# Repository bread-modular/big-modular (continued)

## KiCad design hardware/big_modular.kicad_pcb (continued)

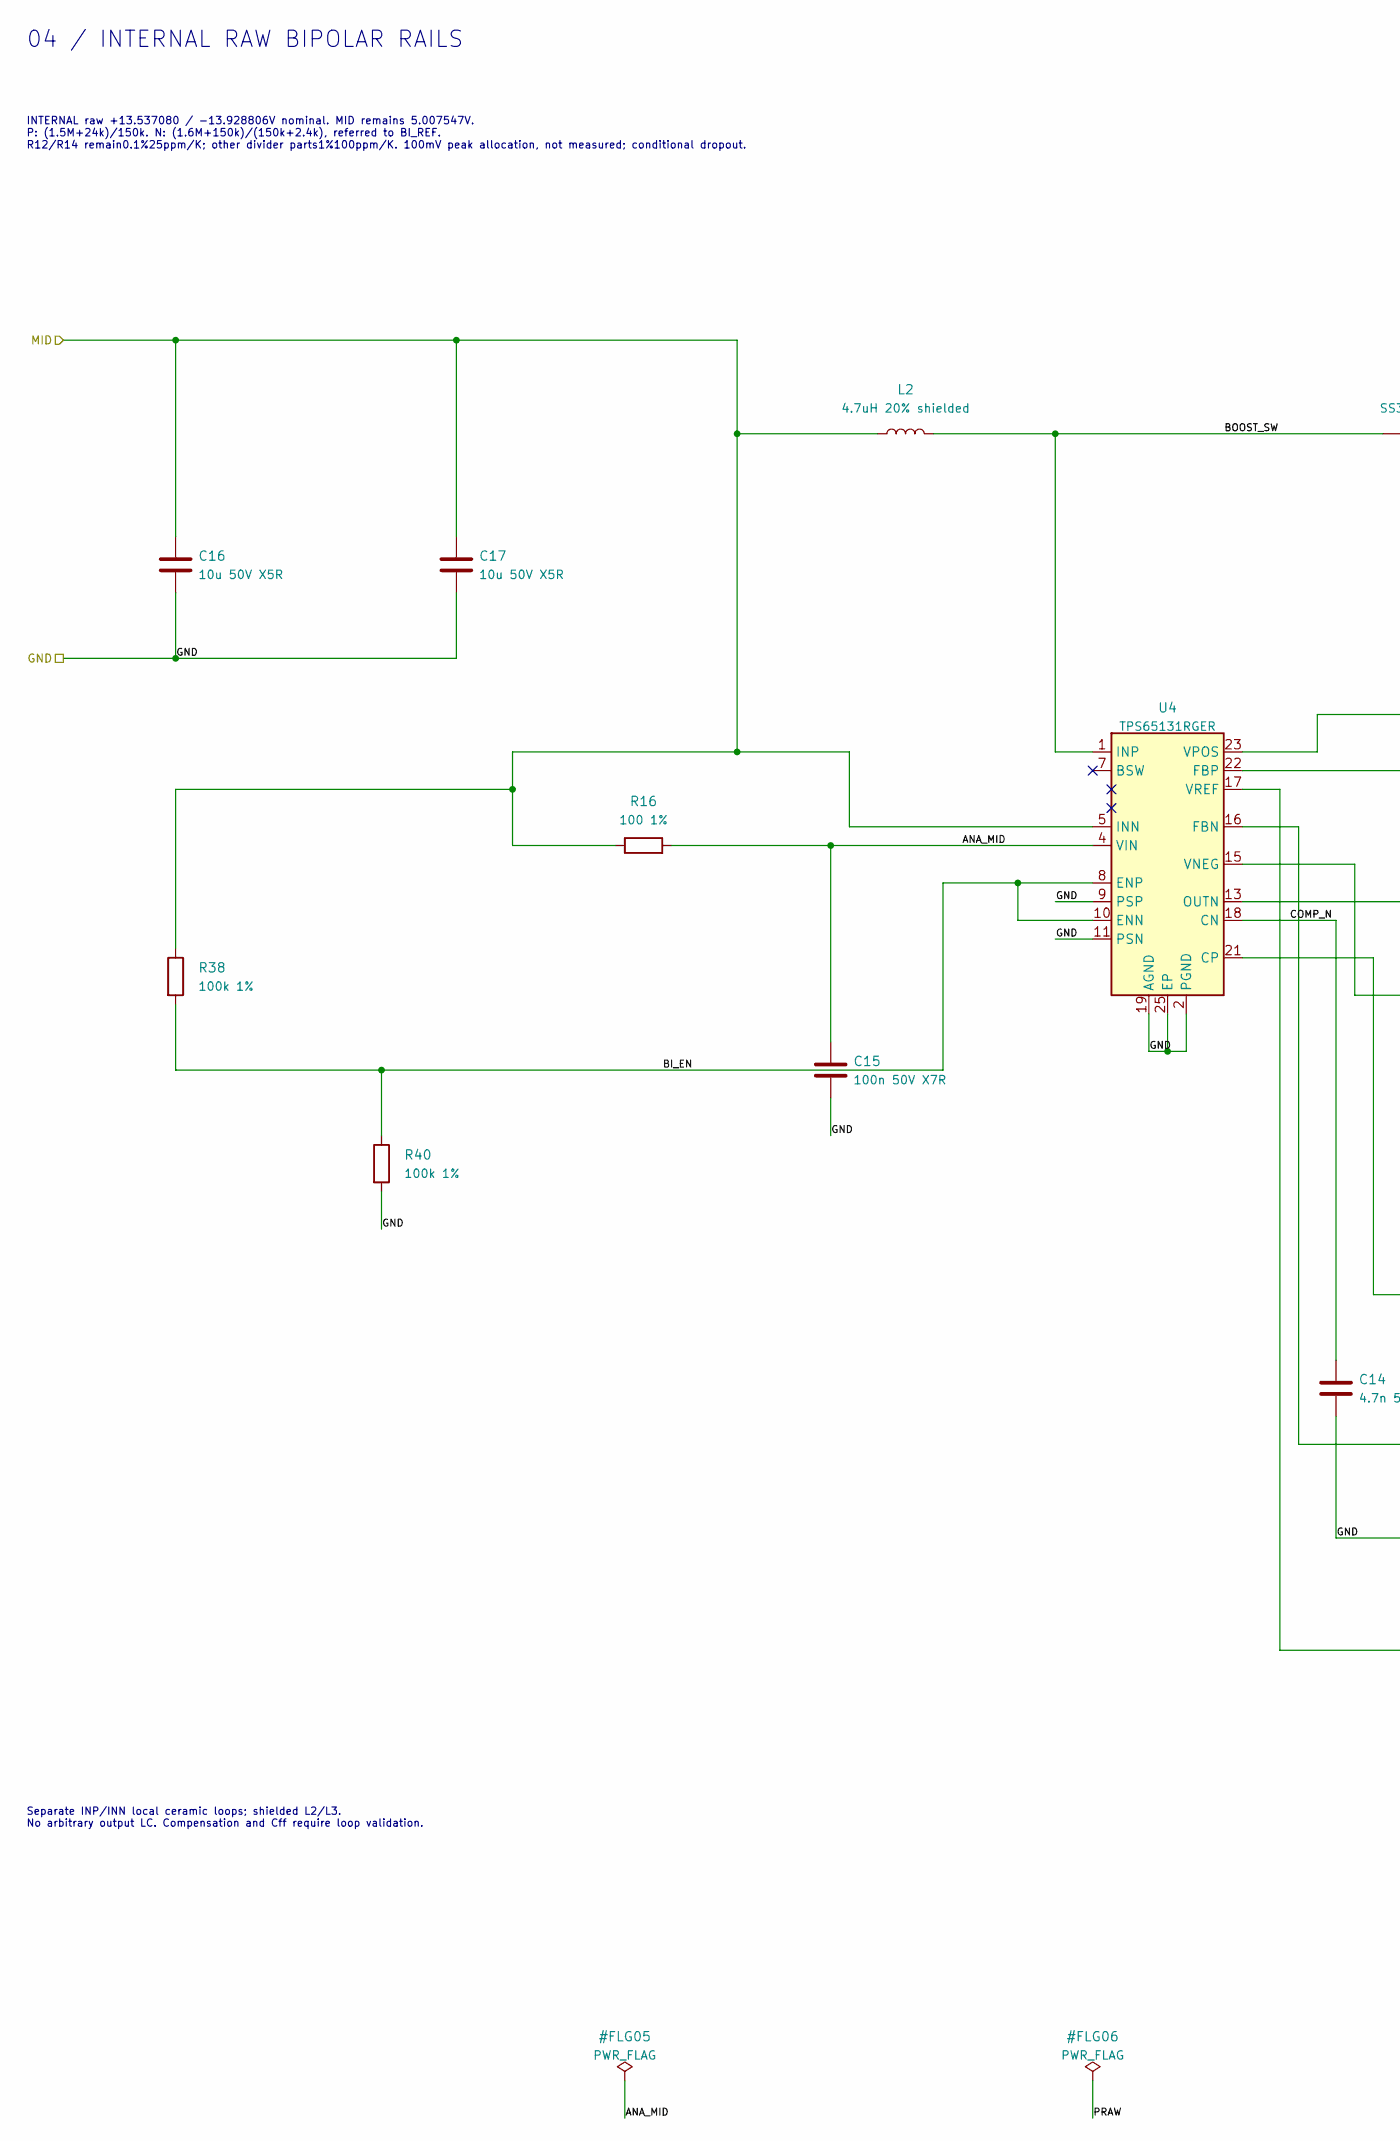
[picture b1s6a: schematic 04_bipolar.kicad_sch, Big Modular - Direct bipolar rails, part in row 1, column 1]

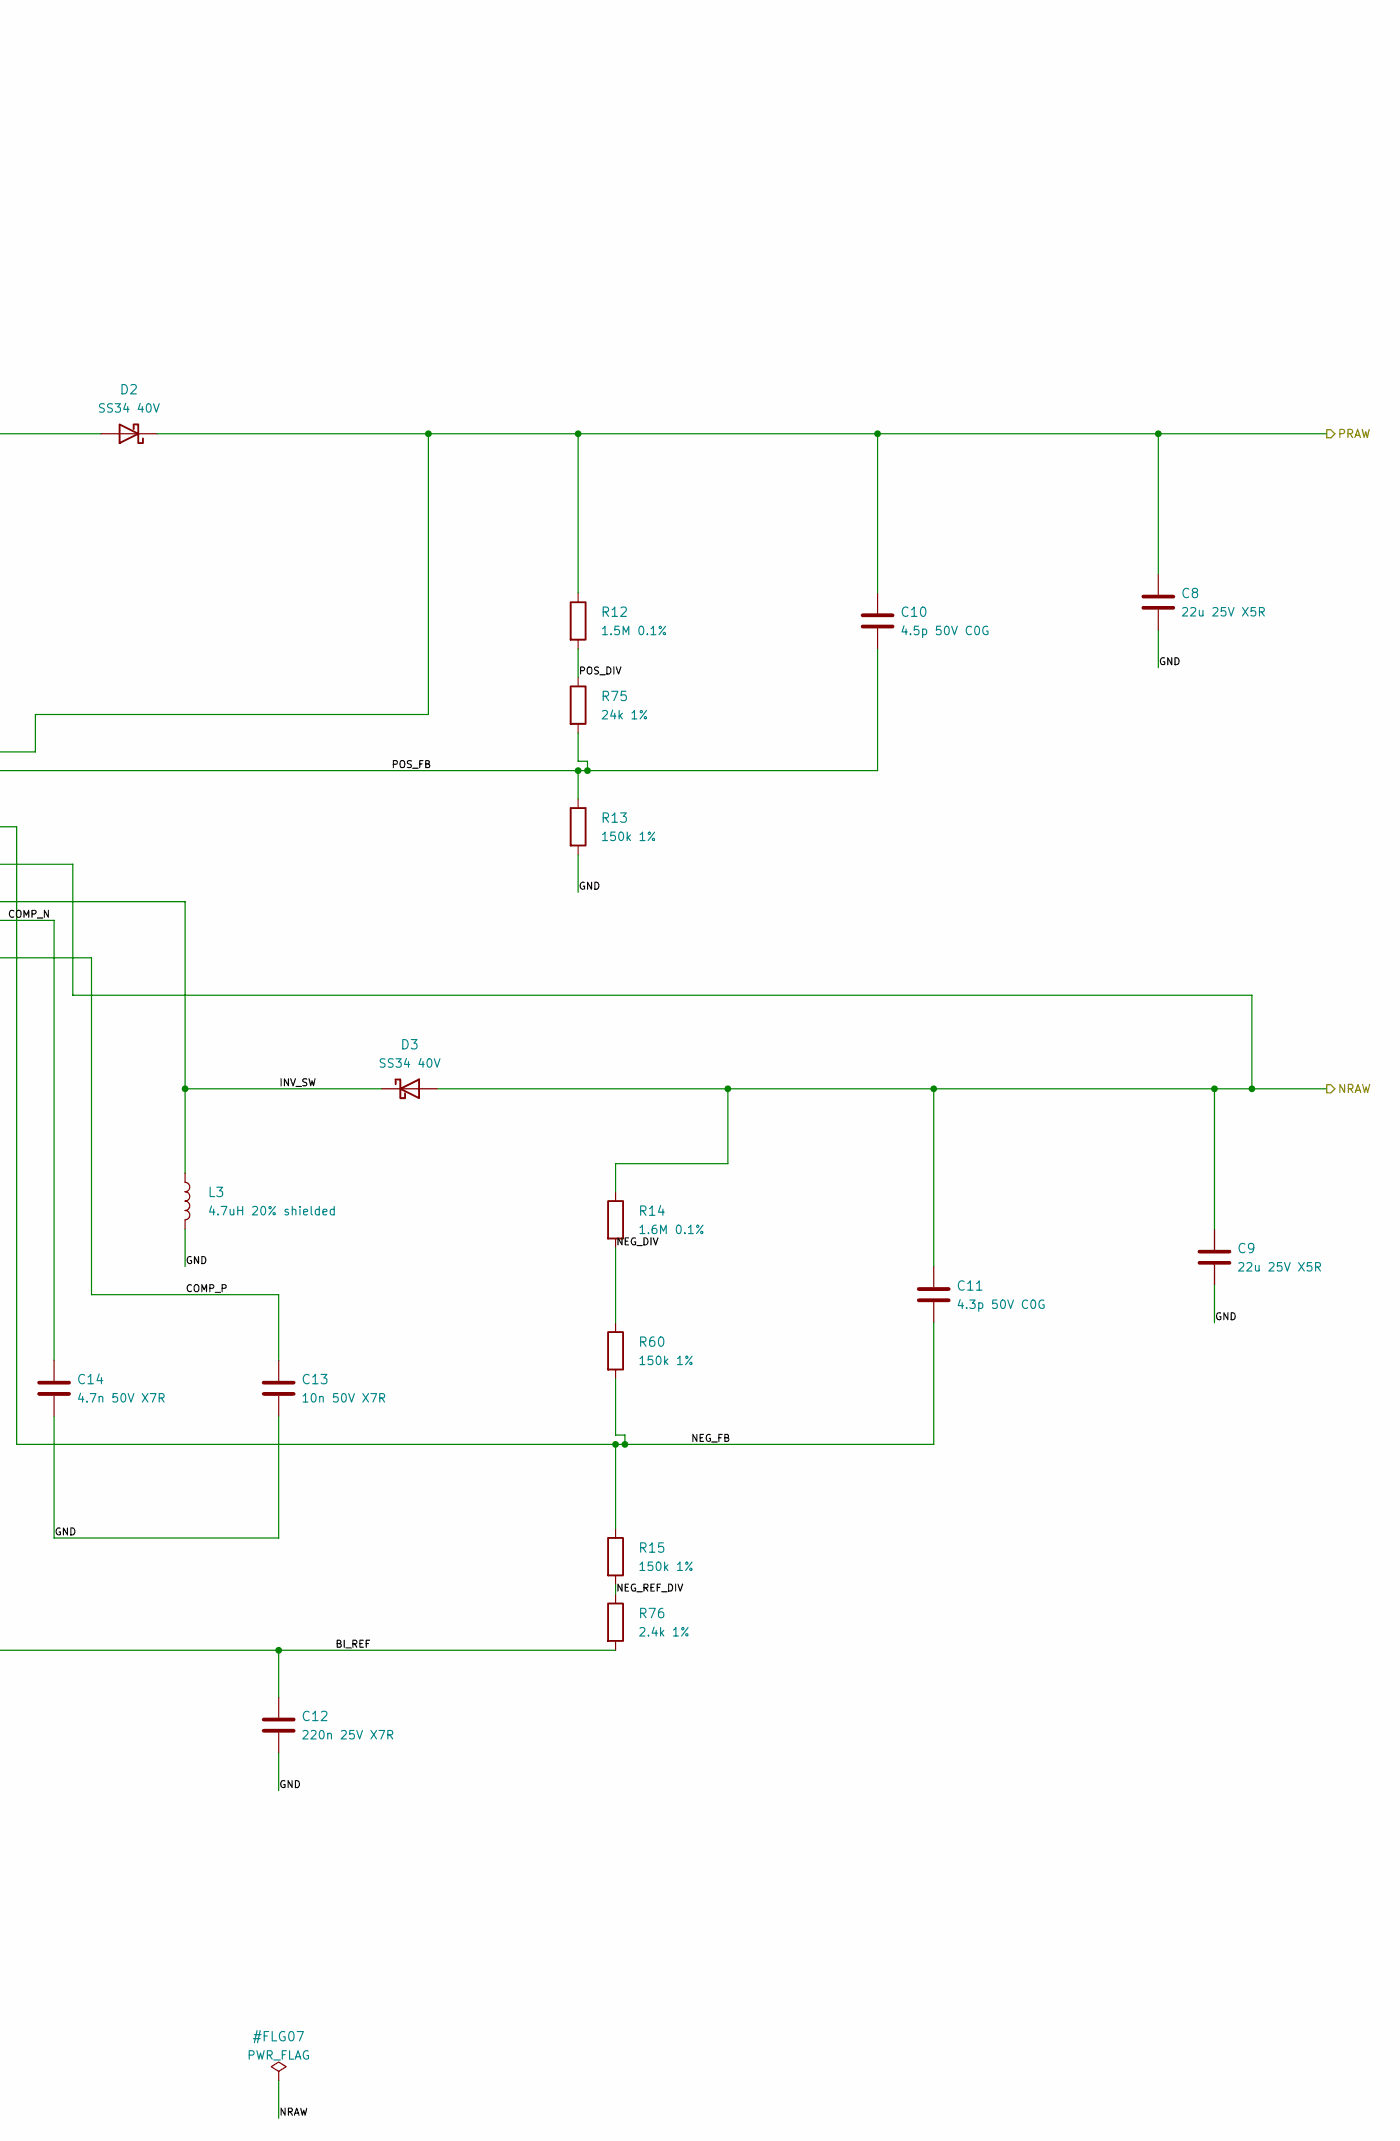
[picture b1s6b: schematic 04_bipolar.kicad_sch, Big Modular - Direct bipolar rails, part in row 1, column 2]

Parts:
C8, C9: 22u 25V X5R; C_1206_3216Metric; MPN CL31A226KAHNNNE; LCSC C12891
C10: 4.5p 50V C0G; C_0402_1005Metric; MPN 0402CG4R5C500NT; LCSC C501829
C11: 4.3p 50V C0G; C_0603_1608Metric; MPN CC0603CRNPO9BN4R3; LCSC C519375
C12: 220n 25V X7R; C_0603_1608Metric; MPN CL10B224KA8NNNC; LCSC C21120
C13: 10n 50V X7R; C_0603_1608Metric; MPN 0603B103K500NT; LCSC C57112
C14: 4.7n 50V X7R; C_0603_1608Metric; MPN 0603B472K500NT; LCSC C53987
C15: 100n 50V X7R; C_0603_1608Metric; MPN CC0603KRX7R9BB104; LCSC C14663
C16, C17: 10u 50V X5R; C_1206_3216Metric; MPN CL31A106KBHNNNE; LCSC C13585
D2, D3: SS34 40V; D_SMA; MPN SS34; LCSC C8678
L2, L3: 4.7uH 20% shielded; L_CENKER_CKCS6045; MPN CKCS6045-4.7uH/M; LCSC C5291878
R12: 1.5M 0.1%; R_0805_2012Metric; MPN CPF0805B1M5E1; LCSC C4223894
R13, R15, R60: 150k 1%; R_0603_1608Metric; MPN 0603WAF1503T5E; LCSC C22807
R14: 1.6M 0.1%; R_0805_2012Metric; MPN CPF0805B1M6E1; LCSC C2088870
R16: 100 1%; R_0603_1608Metric; MPN 0603WAF1000T5E; LCSC C22775
R38, R40: 100k 1%; R_0603_1608Metric; MPN 0603WAF1003T5E; LCSC C25803
R75: 24k 1%; R_0603_1608Metric; MPN 0603WAF2402T5E; LCSC C23352
R76: 2.4k 1%; R_0603_1608Metric; MPN 0603WAF2401T5E; LCSC C22940
U4: TPS65131RGER; Texas_RGE0024B_VQFN-24-1EP_4x4mm_P0.5mm_EP2.45x2.45mm; MPN TPS65131RGER; LCSC C87663

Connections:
/Direct bipolar rails/ANA_MID: C15.1, R16.2, U4.4 (VIN)
/Direct bipolar rails/BI_EN: R38.2, R40.1, U4.8 (ENP), U4.10 (ENN)
/Direct bipolar rails/BI_REF: C12.1, R76.2, U4.17 (VREF)
/Direct bipolar rails/BOOST_SW: D2.2 (A), L2.2, U4.1 (INP), U4.24 (INP)
/Direct bipolar rails/COMP_N: C14.1, U4.18 (CN)
/Direct bipolar rails/COMP_P: C13.1, U4.21 (CP)
/Direct bipolar rails/INV_SW: D3.1 (K), L3.1, U4.13 (OUTN), U4.14 (OUTN)
/Direct bipolar rails/NEG_DIV: R14.2, R60.1
/Direct bipolar rails/NEG_FB: C11.2, R15.1, R60.2, U4.16 (FBN)
/Direct bipolar rails/NEG_REF_DIV: R15.2, R76.1
/Direct bipolar rails/NRAW: C9.1, C11.1, D3.2 (A), R14.1, U4.15 (VNEG); also elsewhere on the board
/Direct bipolar rails/POS_DIV: R12.2, R75.1
/Direct bipolar rails/POS_FB: C10.2, R13.1, R75.2, U4.22 (FBP)
/Direct bipolar rails/PRAW: C8.1, C10.1, D2.1 (K), R12.1, U4.23 (VPOS); also elsewhere on the board
/GND: C8.2, C9.2, C12.2, C13.2, C14.2, C15.2, C16.2, C17.2, L3.2, R13.2, R40.2, U4.2 (PGND), U4.3 (PGND), U4.9 (PSP), U4.11 (PSN), U4.19 (AGND), U4.25 (EP); also elsewhere on the board
/MID: C16.1, C17.1, L2.1, R16.1, R38.1, U4.5 (INN), U4.6 (INN); also elsewhere on the board

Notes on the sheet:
Separate INP/INN local ceramic loops; shielded L2/L3. No arbitrary output LC. Compensation and Cff require loop validation.
04 / INTERNAL RAW BIPOLAR RAILS
INTERNAL raw +13.537080 / -13.928806V nominal. MID remains 5.007547V. P: (1.5M+24k)/150k. N: (1.6M+150k)/(150k+2.4k), referred to BI_REF. R12/R14 remain0.1%25ppm/K; other divider parts1%100ppm/K. 100mV peak allocation, not measured; conditional dropout.

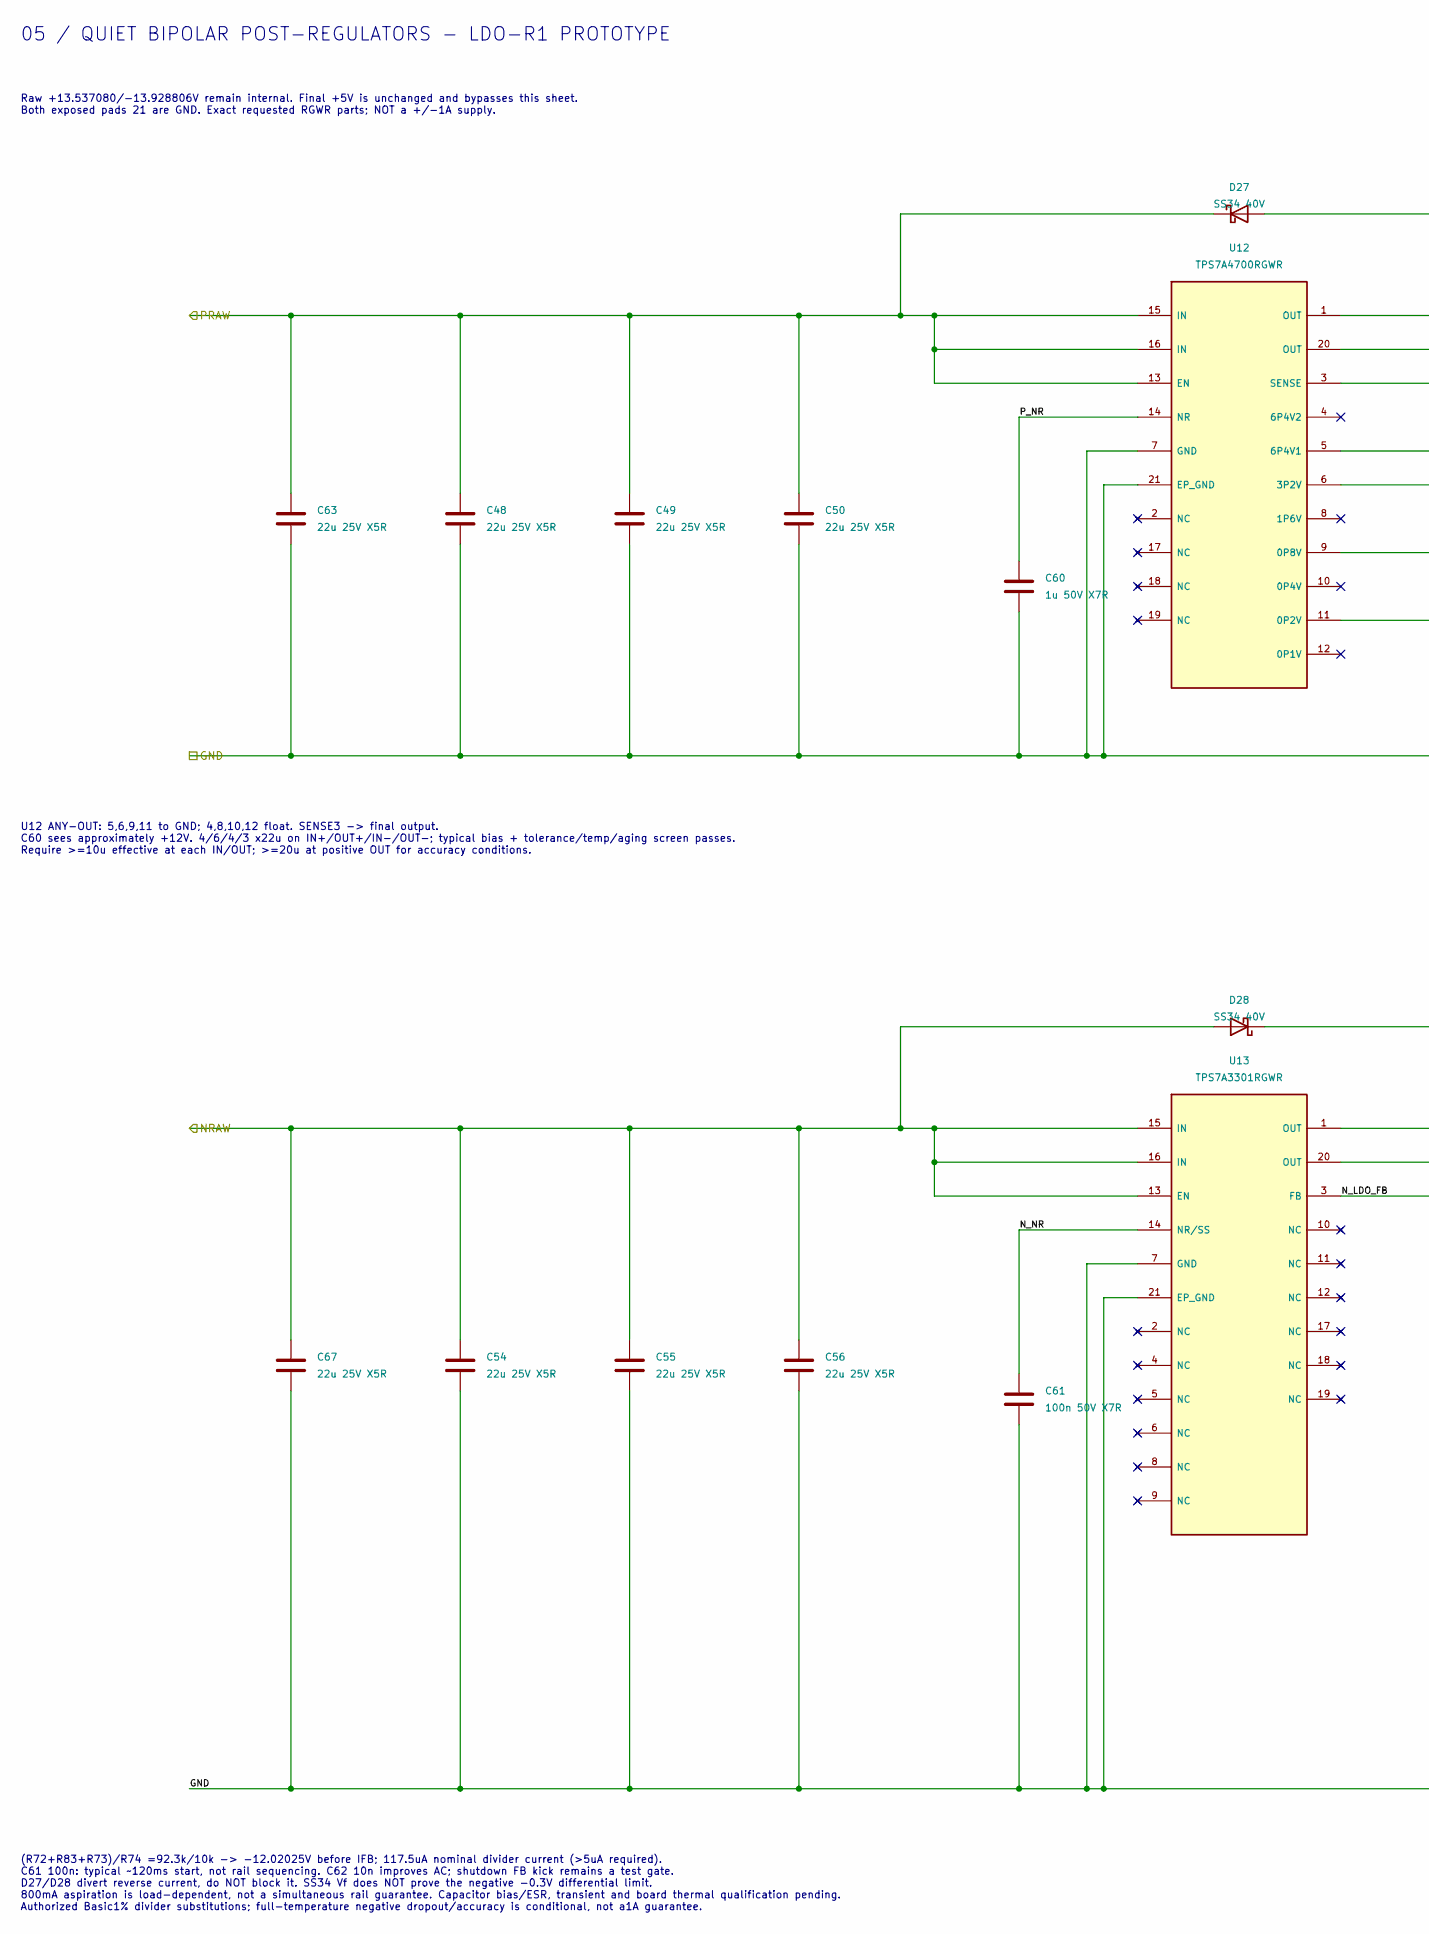
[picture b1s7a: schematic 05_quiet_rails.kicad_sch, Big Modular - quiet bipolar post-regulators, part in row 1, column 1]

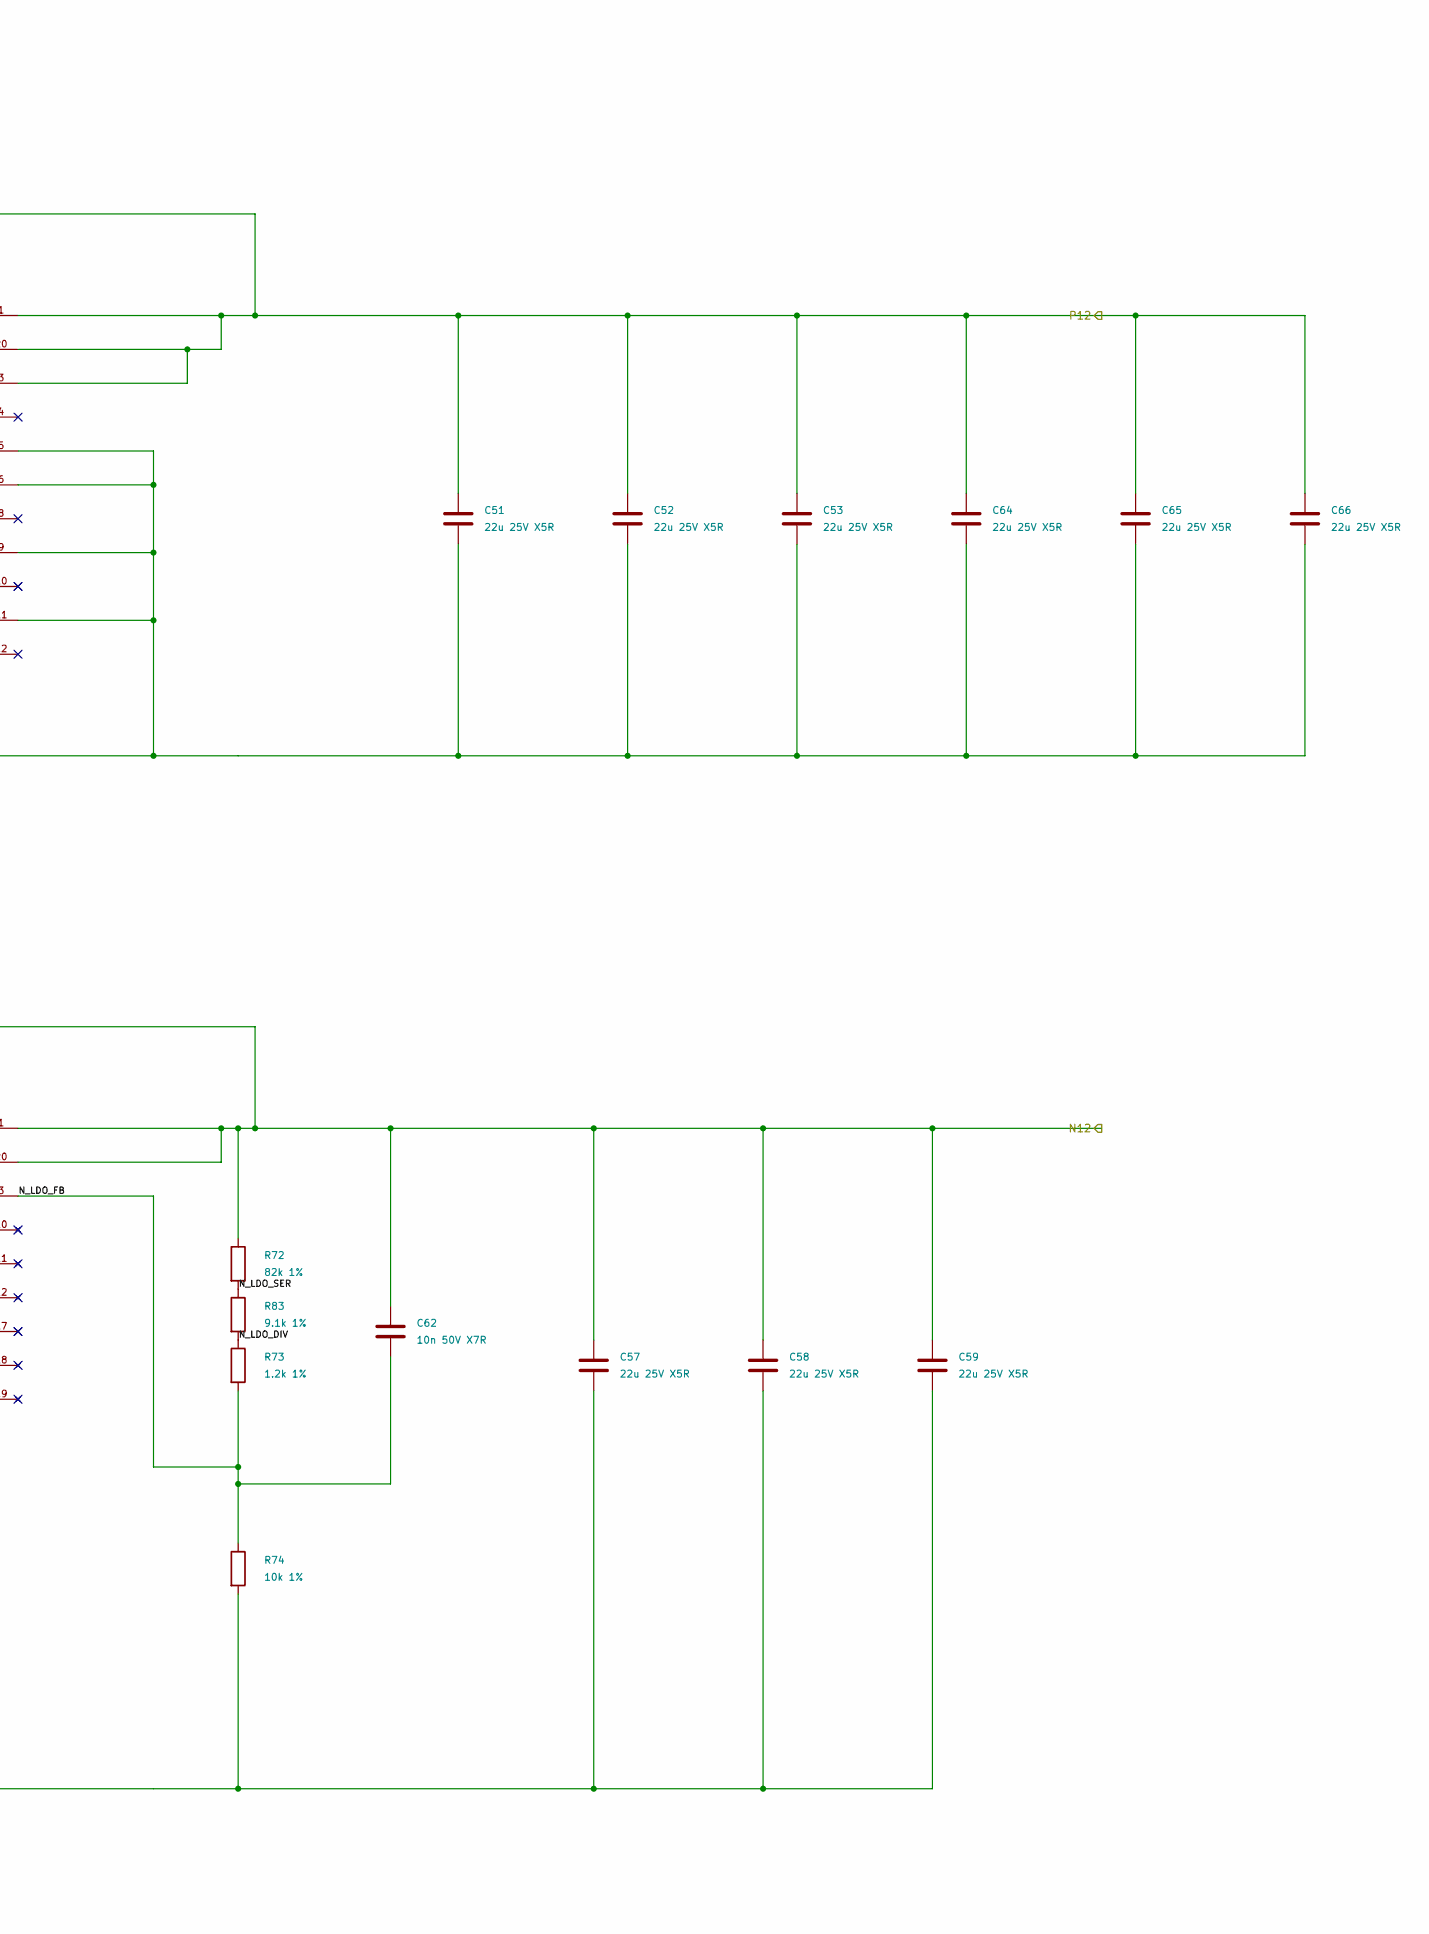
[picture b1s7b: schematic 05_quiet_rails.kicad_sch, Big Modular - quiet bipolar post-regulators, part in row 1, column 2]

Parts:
C48, C49, C50, C51, C52, C53, C54, C55, C56, C57, C58, C59, C63, C64, C65, C66, C67: 22u 25V X5R; C_1206_3216Metric; MPN CL31A226KAHNNNE; LCSC C12891
C60: 1u 50V X7R; C_0805_2012Metric; MPN CL21B105KBFNNNE; LCSC C28323
C61: 100n 50V X7R; C_0603_1608Metric; MPN CC0603KRX7R9BB104; LCSC C14663
C62: 10n 50V X7R; C_0603_1608Metric; MPN 0603B103K500NT; LCSC C57112
D27, D28: SS34 40V; D_SMA; MPN SS34; LCSC C8678
R72: 82k 1%; R_0603_1608Metric; MPN 0603WAF8202T5E; LCSC C23254
R73: 1.2k 1%; R_0603_1608Metric; MPN 0603WAF1201T5E; LCSC C22765
R74: 10k 1%; R_0603_1608Metric; MPN 0603WAF1002T5E; LCSC C25804
R83: 9.1k 1%; R_0603_1608Metric; MPN 0603WAF9101T5E; LCSC C23260
U12: TPS7A4700RGWR; Texas_RGW0020A_VQFN-20-1EP_5x5mm_P0.65mm_EP3.15x3.15mm; MPN TPS7A4700RGWR; LCSC C114839
U13: TPS7A3301RGWR; Texas_RGW0020A_VQFN-20-1EP_5x5mm_P0.65mm_EP3.15x3.15mm; MPN TPS7A3301RGWR; LCSC C90082

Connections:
/Direct bipolar rails/NRAW: C54.1, C55.1, C56.1, C67.1, D28.2 (A), U13.13 (EN), U13.15 (IN), U13.16 (IN); also elsewhere on the board
/Direct bipolar rails/PRAW: C48.1, C49.1, C50.1, C63.1, D27.1 (K), U12.13 (EN), U12.15 (IN), U12.16 (IN); also elsewhere on the board
/GND: C48.2, C49.2, C50.2, C51.2, C52.2, C53.2, C54.2, C55.2, C56.2, C57.2, C58.2, C59.2, C60.2, C61.2, C63.2, C64.2, C65.2, C66.2, C67.2, R74.2, U12.5 (6P4V1), U12.6 (3P2V), U12.7 (GND), U12.9 (0P8V), U12.11 (0P2V), U12.21 (EP_GND), U13.7 (GND), U13.21 (EP_GND); also elsewhere on the board
/N12: C57.1, C58.1, C59.1, C62.1, D28.1 (K), R72.1, U13.1 (OUT), U13.20 (OUT); also elsewhere on the board
/P12: C51.1, C52.1, C53.1, C64.1, C65.1, C66.1, D27.2 (A), U12.1 (OUT), U12.3 (SENSE), U12.20 (OUT); also elsewhere on the board
/Quiet bipolar post-regulators/N_LDO_DIV: R73.1, R83.2
/Quiet bipolar post-regulators/N_LDO_FB: C62.2, R73.2, R74.1, U13.3 (FB)
/Quiet bipolar post-regulators/N_LDO_SER: R72.2, R83.1
/Quiet bipolar post-regulators/N_NR: C61.1, U13.14 (NR/SS)
/Quiet bipolar post-regulators/P_NR: C60.1, U12.14 (NR)

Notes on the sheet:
05 / QUIET BIPOLAR POST-REGULATORS - LDO-R1 PROTOTYPE
Raw +13.537080/-13.928806V remain internal. Final +5V is unchanged and bypasses this sheet. Both exposed pads 21 are GND. Exact requested RGWR parts; NOT a +/-1A supply.
U12 ANY-OUT: 5,6,9,11 to GND; 4,8,10,12 float. SENSE3 -> final output. C60 sees approximately +12V. 4/6/4/3 x22u on IN+/OUT+/IN-/OUT-; typical bias + tolerance/temp/aging screen passes. Require >=10u effective at each IN/OUT; >=20u at positive OUT for accuracy conditions.
(R72+R83+R73)/R74 =92.3k/10k -> -12.02025V before IFB; 117.5uA nominal divider current (>5uA required). C61 100n: typical ~120ms start, not rail sequencing. C62 10n improves AC; shutdown FB kick remains a test gate. D27/D28 divert reverse current, do NOT block it. SS34 Vf does NOT prove the negativ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

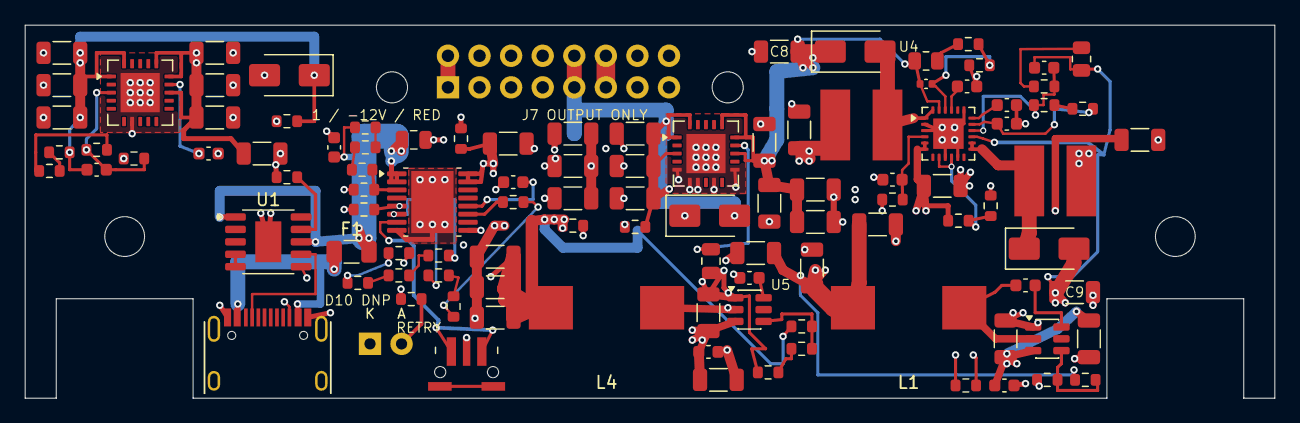
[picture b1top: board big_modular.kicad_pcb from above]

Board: 4 copper layers, 100.5 x 30.0 mm, 107 parts (0 on the bottom side), 53 nets.
